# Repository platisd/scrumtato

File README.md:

# Scrumtato
Scrumtato is an ATtiny85-based gadget to keep overly passionate developers from excessively talking during daily stand-up meetings. The name stems from the combination of [SCRUM](https://en.wikipedia.org/wiki/Scrum_(software_development)) and [Hot Potato](https://en.wikipedia.org/wiki/Hot_potato_(game)).

## About Scrumtato
During our daily stand-up meetings (SCRUM), as we are a team full of talented and passionate developers, we just love to talk too much. This stretches our meeting and keeps us from getting the most out of our working hours. To solve this problem, here comes **Scrumtato: A gadget to make daily stand-ups agile again!**

## How does it work
Operating the Scrumtato is simple!
1. Press the button when you are ready to talk. You will hear 2 beeps.
2. Start talking. You have to concisely explain what you did since the last meeting and what you are planning to do until the next.
3. If you finish before the time runs out (in which case the Scrumtato will beep and vibrate), press the button again. You will hear 3 beeps.

### More details
The user begins interacting with the Scrumtato by pressing the on-board button and starts talking about all the extraordinary things they got into since the last daily stand-up. This initiates a countdown timer that lasts as long as each team member is supposed to speak. To indicate that half of the remaining time has just been depleted, Scrumtato will beep once. For example, if the total available period for someone to speak is 1 minute, the user will hear beeps on approximately the 30th, 45th, 52nd, 56th, 58th and 59th seconds. As soon as the time is up, a characteristic beep sequence is played and Scrumato vibrates.

In other words, Scrumtato can be considered as a stress ball that... actually stresses you out! If the team member finishes talking in a timely manner, then they merely need to press the button again and a sound sequence that indicates the successful end of a turn is played.

From a technical perspective, since the users should not have to change the battery often, the microcontroller will go to sleep as much as possible. That is between "games" and between beeps or vibrations during the "games". In the former case, the microcontroller is woken up by the button press and in the latter by a watchdog timer.

## Other uses
Scrumtato was initially conceived as a toy for kids (or grown ups, no judging) and particularly, as a way to play Hot Potato. This use case is supported separately from the main one, however their integration into a common program should not be complicated as they share logic and states.

Specifically, the watchdog timer is triggered faster and the buzzer beeps when 5% of the remaining time is depleted, therefore more frequently compared to the stand-up scenario. Additionally, the on-board analog accelerometer is utilized to determine if a player does not pass the ball fast enough. In that case, a faster countdown is initiated and the ball must be passed in a couple of seconds otherwise it "explodes" in the hands of the one that was delaying the game. This increases the suspense and the pace of the game.

The Hot Potato use case is not supported since `rev.3` as the accelerometer was removed. If you want to download that specific version then do `git checkout -b hw_rev.2`.

## Software
The use cases supported by Scrumtato can be found in the [firmware](https://github.com/platisd/scrumtato/tree/master/firmware) directory.

* [Standup Potato](https://github.com/platisd/scrumtato/tree/master/firmware/StandupPotato): The way to make daily stand-ups agile again
* [Hot Potato](https://github.com/platisd/scrumtato/tree/master/firmware/HotPotato): A modern and suspenseful take on the classic Hot Potato game, supported up to `rev.2` hardware.

## Hardware
From a physical perspective, Scrumtato is comprised of a PCB and a 3D-printed case to protect the electronics as well as make passing around easier and more fun.

### PCB
The printed circuit board was designed with [Eagle CAD](https://www.autodesk.com/products/eagle/overview) and the latest `rev. 3` boards were fabricated by [PCBWay](https://www.pcbway.com/project/shareproject/Scrumtato__Make_daily_standups_agile_again__rev_3_.html). Using the above service you can preview your board, as well as any changes you made, before ordering it and have it nicely packaged and delivered to your address in less than a week.

### 3D printed cases
Depending on the how you use Scrumtato, different case should be utilized. When used as a stand-up meeting gadget, it is *probably* not going to be thrown around. Therefore a case from common PLA plastic will work just fine. However, if kids come into the equation a flexible case is strongly suggested, since the gadget will be mishandled and dropped on the floor. After all, this is part of the fun. The flexible version was printed with a [ZYYX+ printer](http://www.zyyx3dprinter.com/), using their proFLEX filament. The PLA version was printed with a [Micro M3D printer](https://printm3d.com/themicro/). The models were sliced with Simplify3D. If you need more information on the specific Simplify3D profiles used, tips on how to print (e.g. when to use support etc) or the source of the models, please contact me.

* [Scrumtato PLA version](https://github.com/platisd/scrumtato/tree/master/physibles/pla) - To be used during the daily stand-up meetings.
* [Scrumtato Flex version](https://github.com/platisd/scrumtato/tree/master/physibles/flex) - To be used as a toy for kids.

### Components
* **[Scrumtato PCB](hardware/)** - You can also [order it from PCBWay](https://www.pcbway.com/project/shareproject/Scrumtato__Make_daily_standups_agile_again__rev_3_.html)
* **Four M3x10 flat head screws** - To mount the board. Longer ones (until M3x40) will also work.
* **Two M3x20 flat head screws** - To keep the upper and bottom part of the case together. Longer ones (until M3x40) will also work. **Only for the toy/flexible version!**
* **CR2032 battery** - To power everything up
* **CR2032 battery holder** - To keep the battery in place. Get the through-hole version.
* **ATtiny85-20PU** - If you only want to use it during stand-up meetings, then an **ATtiny25-20PU** will suffice.
* **DIP-8 socket** - Optional, but will probably make your life easier if you need to remove the microcontroller in order to reprogram it.
* **9mm Buzzer** - They are not the most common but take up less space. I might consider replacing them in the future with something easier to source.
* **22Ω 1206 resistor** - Used for the buzzer. Other low valued resistors will probably work as well.
* **SMD vibrating motor** - To make Scrumtato vibrate. The board is modeled after Sanyo NRS-2574 but all other models that fit the dimensions will work.
* **4-pin tactile switch** - To initiate (or finish occasionally) the game. Get the through-hole version.
* **2-pin angled switch** - As a reset button. Through-hole component.
* **LED 5mm** - Optional and rather unnecessary when using the flexible version since it is not visible.
* **220Ω 1206 resistor** - Optional unless the LED is used.
* **BC547 NPN transistor** - To control the vibration motor.
* **1KΩ 1206 resistor** - To drive the transistor.
* **Two 10KΩ 1206 resistors** - Used as pull ups. One for the microcontroller's reset pin and the other for the tactile switch.
* **Hot Potato toy** - Optionally supported up to hardware `rev.2`
  * **GY-61 accelerometer module** - Based on the ADXL335 chip. Try to get one that has its pins unsoldered.
  * **5-pin angled male header** - To solder on the GY-61 module in order to mount it vertically on the board.
  * **5-pin female header** - So you do not to have to solder the GY-61 module.

## Articles
[Scrumtato: Make daily stand-ups agile again](https://platis.solutions/blog/2017/06/12/scrumtato-make-daily-stand-ups-agile-again/)

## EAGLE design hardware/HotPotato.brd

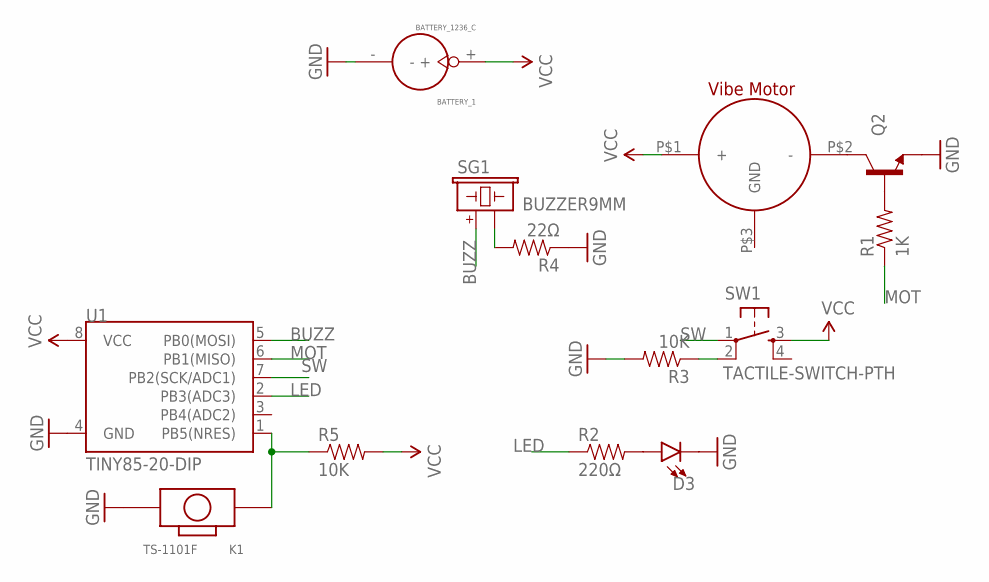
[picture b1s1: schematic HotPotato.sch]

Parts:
BATTERY_1: BATTERY_1236_C
D3: LED5MM-KIT; LED_5MM-KIT
K1: TS-1101F; SW2-3.4X6.0X3.55MM-90D
M1: SANYO_NRS-2574SMT; SMT
Q2: TRANSISTOR_NPNBC547; TO-92-AMMO
R1: 1K; 1206
R2: 220Ω; 1206
R3, R5: 10K; 1206
R4: 22Ω; 1206
SG1: BUZZER9MM; BUZZER-9MM-PTH_NEW
SW1: TACTILE-SWITCH-PTH; TAC-SWITCH-PTH
U1: TINY85-20-DIP; DIP08

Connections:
BUZZ: SG1.P$1 (1), U1.5 (PB0(MOSI))
GND: BATTERY_1.-, D3.K (C), K1.P$2 (2), Q2.3 (E), R3.2, R4.1, U1.4 (GND)
LED: R2.1, U1.2 (PB3(ADC3))
MOT: R1.1, U1.6 (PB1(MISO))
unnamed: R3.1, SW1.2
unnamed: D3.A, R2.2
unnamed: M1.P$2 (-), Q2.1 (C)
unnamed: Q2.2 (B), R1.2
unnamed: R4.2, SG1.P$2 (2)
unnamed: K1.P$1 (1), R5.1, U1.1 (PB5(NRES))
SW: SW1.1, U1.7 (PB2(SCK/ADC1))
VCC: BATTERY_1.+, M1.P$1 (+), R5.2, SW1.3, U1.8 (VCC)

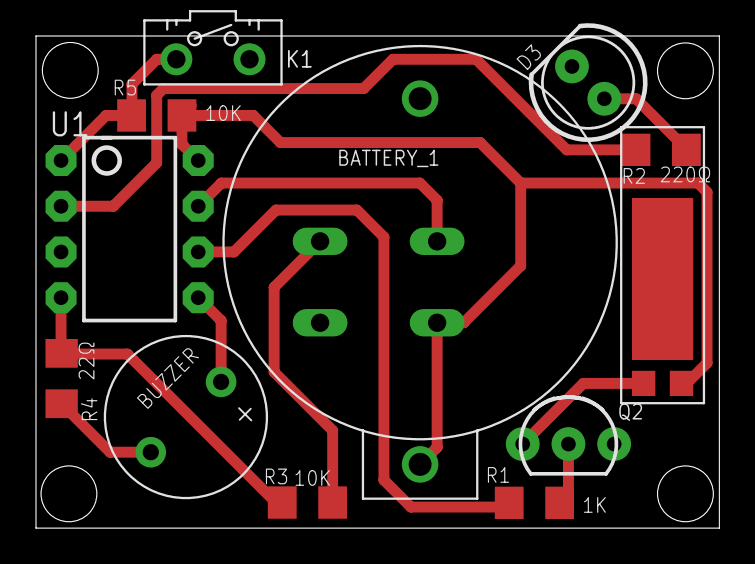
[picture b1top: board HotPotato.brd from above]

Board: 2 copper layers, 38.0 x 27.3 mm, 14 parts (1 on the bottom side), 12 nets.

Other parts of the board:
U$1: OSHWLOGO_BACK_0.2

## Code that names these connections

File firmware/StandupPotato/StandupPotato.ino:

#include <avr/sleep.h>
#include <avr/power.h>
#include <avr/wdt.h>

enum WatchDogTimeout {
  WDT_16ms = 0,
  WDT_32ms,
  WDT_64ms,
  WDT_128ms,
  WDT_250ms,
  WDT_500ms,
  WDT_1sec,
  WDT_2sec,
  WDT_4sec,
  WDT_8sec
};

enum PowerState {
  DEEP_SLEEP,
  GAME
};

const unsigned int BUZZER_PIN = PB0;
const unsigned int MOTOR_PIN = PB1;
const unsigned int BUTTON_PIN = PB2;
const unsigned int LED_PIN = PB3;

const unsigned long TURN_DURATION = 60000; // The time in milliseconds that each person can talk
unsigned long halfOfRemainingTime = TURN_DURATION / 2;
volatile bool watchDogBarked = false;
bool watchDogEnabled = false;
const WatchDogTimeout gameWdt = WDT_1sec;

WatchDogTimeout currentWdt = gameWdt;
unsigned long elapsedTime = 0; // How much time has elapsed in the running turn in milliseconds

volatile bool buttonPressed = false;

const unsigned long remindBeepDuration = 150; // How long in milliseconds we should beep to "stress" the user

PowerState currentState = DEEP_SLEEP; // Start with sleep as the initial state

/**
      Utility method that turns the LED on
*/
void turnLightOn() {
  digitalWrite(LED_PIN, HIGH);
}

/**
      Utility method that turns the LED off
*/
void turnLightOff() {
  digitalWrite(LED_PIN, LOW);
}

/**
   Vibrate for the specified amount of time (blocking)
   @param duration milliseconds the motor will vibrate
*/
void vibrateFor(unsigned long duration) {
  startVibrating();
  delay(duration);
  stopVibrating();
}

/**
   Utility method that starts the vibrating motor
*/
void startVibrating() {
  digitalWrite(MOTOR_PIN, HIGH);
}

/**
   Utility method that stops the vibrating motor
*/
void stopVibrating() {
  digitalWrite(MOTOR_PIN, LOW);
}

/**
   Ring the buzzer for the specified amount of time (blocking) while lighting the LED
   @param duration milliseconds the buzzer will ring
*/
void ringFor(unsigned long duration) {
  startRinging();
  turnLightOn();
  delay(duration);
  turnLightOff();
  stopRinging();
}

/**
   Utility method that starts ringing the buzzer
*/
void startRinging() {
  digitalWrite(BUZZER_PIN, HIGH);
}

/**
   Utility method that stops ringing the buzzer
*/
void stopRinging() {
  digitalWrite(BUZZER_PIN, LOW);
}

/**
   A utility method to derive a watchdog timeout's duration
   @return the amount of milliseconds corresponding to a watchdog timeout
*/
unsigned long getTimeoutDuration() {
  return 1 << (currentWdt + 4);
}

void setupWatchDogTimeoutOneshot(WatchDogTimeout wdt) {
  // Adopted from InsideGadgets (www.insidegadgets.com)
  byte timeoutVal = wdt & 7;
  if (wdt > 7) {
    timeoutVal |= (1 << 5);
  }
  timeoutVal |= (1 << WDCE);

  MCUSR &= ~(1 << WDRF);
  WDTCR |= (1 << WDCE) | (1 << WDE); // Start timed sequence
  WDTCR = timeoutVal;
  WDTCR |= _BV(WDIE);
  wdt_reset();  // pat the dog
  currentWdt = wdt;
}

/**
  Watchdog interrupt routine to be triggered when watchdog times out
*/
ISR(WDT_vect) {
  watchDogBarked = true;
  wdt_disable(); // disable watchdog
}

/**
   Change interrupt routine (e.g. when button presses occur)
*/
ISR (PCINT0_vect) {
  // TO-DO: Investigate ways to debounce the button
  if (digitalRead(BUTTON_PIN) == LOW) {
    buttonPressed = true;
  }
}

/**
   Sets up pin change interrupt for PB2
*/
void setupChangeInterrupt() {
  PCMSK |= bit (PCINT2); // want pin D2 (PB2)
  GIFR |= bit (PCIF); // clear any outstanding interrupts
  GIMSK |= bit (PCIE); // enable pin change interrupts
}

/**
   Sets the MCU into a deep sleep state until a change interrupt is triggered
*/
void goToSleep() {
  set_sleep_mode(SLEEP_MODE_PWR_DOWN);
  ADCSRA = 0; // turn off ADC
  power_all_disable (); // power off ADC, Timer 0 and 1, serial interface
  sleep_enable();
  sleep_cpu(); // Sleep here and wait for the interrupt
  sleep_disable();
  power_all_enable(); // power everything back on
}

void setup() {
  pinMode(BUZZER_PIN, OUTPUT);
  pinMode(MOTOR_PIN, OUTPUT);
  pinMode(BUTTON_PIN, INPUT);
  pinMode(LED_PIN, OUTPUT);
  setupChangeInterrupt();
}

void loop() {
  switch (currentState) {
    case DEEP_SLEEP:
      // Go to deep sleep until an interrupt occurs
      goToSleep();
      // Proceed to the
      if (buttonPressed) {
        // Beep fast twice to indicate the beginning of a game
        ringFor(100);
        delay(100);
        ringFor(100);
        currentState = GAME;
        buttonPressed = false;
      }
      break;
    case GAME:
      // If watchdog is not enabled, then we either just arrived from SLEEP state
      // or from a watchdog bark. Therefore we need to set another watchdog timer.
      if (!watchDogEnabled) {
        // Set up watchdog to be triggered (once) after the specified time
        setupWatchDogTimeoutOneshot(gameWdt);
        watchDogEnabled = true;
      }
      // Go to deep sleep until an interrupt occurs
      goToSleep();
      // We might have gone out of sleep due to another interrupt (i.e. the switch)
      // So make sure that we know what we are doing depending on who interrupted our sleep
      if (watchDogBarked) {
        watchDogBarked = false;
        watchDogEnabled = false;
        elapsedTime += getTimeoutDuration();
        unsigned long remainingTime = TURN_DURATION - elapsedTime;
        /* --- Main game logic --- */
        if (elapsedTime >= TURN_DURATION) {
          // Play a sound and vibration sequence to indicate the end of a game due to timeout
          ringFor(100);
          delay(100);
          ringFor(100);
          delay(300);
          startVibrating();
          ringFor(800);
          stopVibrating();
          currentState = DEEP_SLEEP;
          elapsedTime = 0;
          halfOfRemainingTime = TURN_DURATION / 2; // reset the remaining time since the turn is over
        } else if (remainingTime <= halfOfRemainingTime) {
          // Ring when we reach half of the remaining time available
          ringFor(remindBeepDuration);
          elapsedTime += remindBeepDuration; // Add the time we spent ringing
          halfOfRemainingTime /= 2;
        }
      }
      if (buttonPressed) {
        buttonPressed = false;
        // Ensure that a button press did not occur right after the turn finished
        // (e.g. while playing the timeout ringing sequence) and just before going to sleep
        if (currentState != DEEP_SLEEP) {
          // If the user pressed the button before their time was up, it means that the turn can finish before the time is up
          // Play a sound sequence to indicate the end of a game due to button press
          ringFor(50);
          delay(100);
          ringFor(50);
          delay(100);
          ringFor(50);
          // We don't need the watchdog running anymore, so disable it and reset the related variables
          wdt_disable(); // disable watchdog
          watchDogBarked = false;
          watchDogEnabled = false;
          elapsedTime = 0;
          halfOfRemainingTime = TURN_DURATION / 2; // reset the remaining time since the turn is over
          // Go back to the sleep state
          currentState = DEEP_SLEEP;
        }
      }
      break;
    default:
      break;
  }
}

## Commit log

2017-05-23 Rev. 0 of board
    Known problems:
    * Buzzer footprint needs to have the pins slightly further from each other
2017-05-23 Initial commit with deep sleep and watchdog timer
2017-05-23 Initial empty sketch
2017-05-23 Add gitattributes to ignore the Eagle files
2017-05-27 Add standup potato firmware
    A basic version of the scrumtato (Hot potato for daily standup meetings).
    TO-DO: Accelerometer currently not used. Decide whether to use it or remove
    completely from code.
2017-05-27 Register button pressed on button up
    WIP anyway, this firmware will drastically change
2017-05-28 Beep when remaining time has been reduced to half
2017-05-28 Each team member should talk for 1.5 minutes instead
2017-05-28 Removing unused variables and calculate ring time in elapsed time
2017-05-28 Hot potato game
    For the time being without using the accelerometer
2017-05-30 Decreasing turn time to 60 seconds
    Each team member should not speak more than 1 minute ideally. :)
2017-05-30 Adding accelerometer detection of movement
    The ball can now detect if the user is holding it for too long
    in their hands. If that happens, we start counting down faster so to
    "explode" in case the ball is not passed.
2017-06-01 Decreasing the time to pass the ball when in countdown mode
    Also added more comments to important variables
2017-06-11 Add Scrumtato's 3D models
2017-06-11 Add documentation
2017-06-12 Fix typos and add link to article
2017-06-14 Change LED package to 5mm
    Fixes #2
2017-06-14 Add reset button
    Fixes #1
2017-06-14 Change board name and board revision
2017-06-14 Small mainly commodity fixes
    Changing orientation of D3, placement of R4, SW1 part number placement
2017-06-27 Update components according to rev.1 board
2017-06-28 Add rev. 1 bottom part of the PLA version
    Adds a pin-hole for reset button and a small holder to stop the buttom from bending upwards when pressed
2017-06-29 Add links to purchase board
    From OSHPark and Seeedstudio for rev. 1
2017-06-29 Set theme jekyll-theme-cayman
2017-06-29 Add scrumtato pic and intro text
2017-06-29 Add step-by-step instructions
2017-07-04 Add PCB fab info
2017-10-18 Update relative links to absolute
    This will enable them to appear correctly when opened from scrumtato.com
2017-10-22 Increase distance between buzzer poles
    Fixes #4
2017-11-11 Update manufacturing details for HW rev. 2
2018-05-27 Update documentation for rev.3 hardware
2018-05-27 Remove accelerometer header and set dedicated LED pin
    [hw rev. 3]
    Since the Hot Potato (game) use case was deemed less significant
    hardware support for it was removed in order to leave more space
    for the common components. This also enabled us to use a dedicated
    pin for the LED which was previously routed in parallel with the
    buzzer. This should enable better control over the hardware and
2023-10-10 Fix broken link

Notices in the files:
parts and their libraries:
SparkFun-LED: Licensing: Creative Commons ShareAlike 4.0 International - https://creativecommons.org/licenses/by-sa/4.0
